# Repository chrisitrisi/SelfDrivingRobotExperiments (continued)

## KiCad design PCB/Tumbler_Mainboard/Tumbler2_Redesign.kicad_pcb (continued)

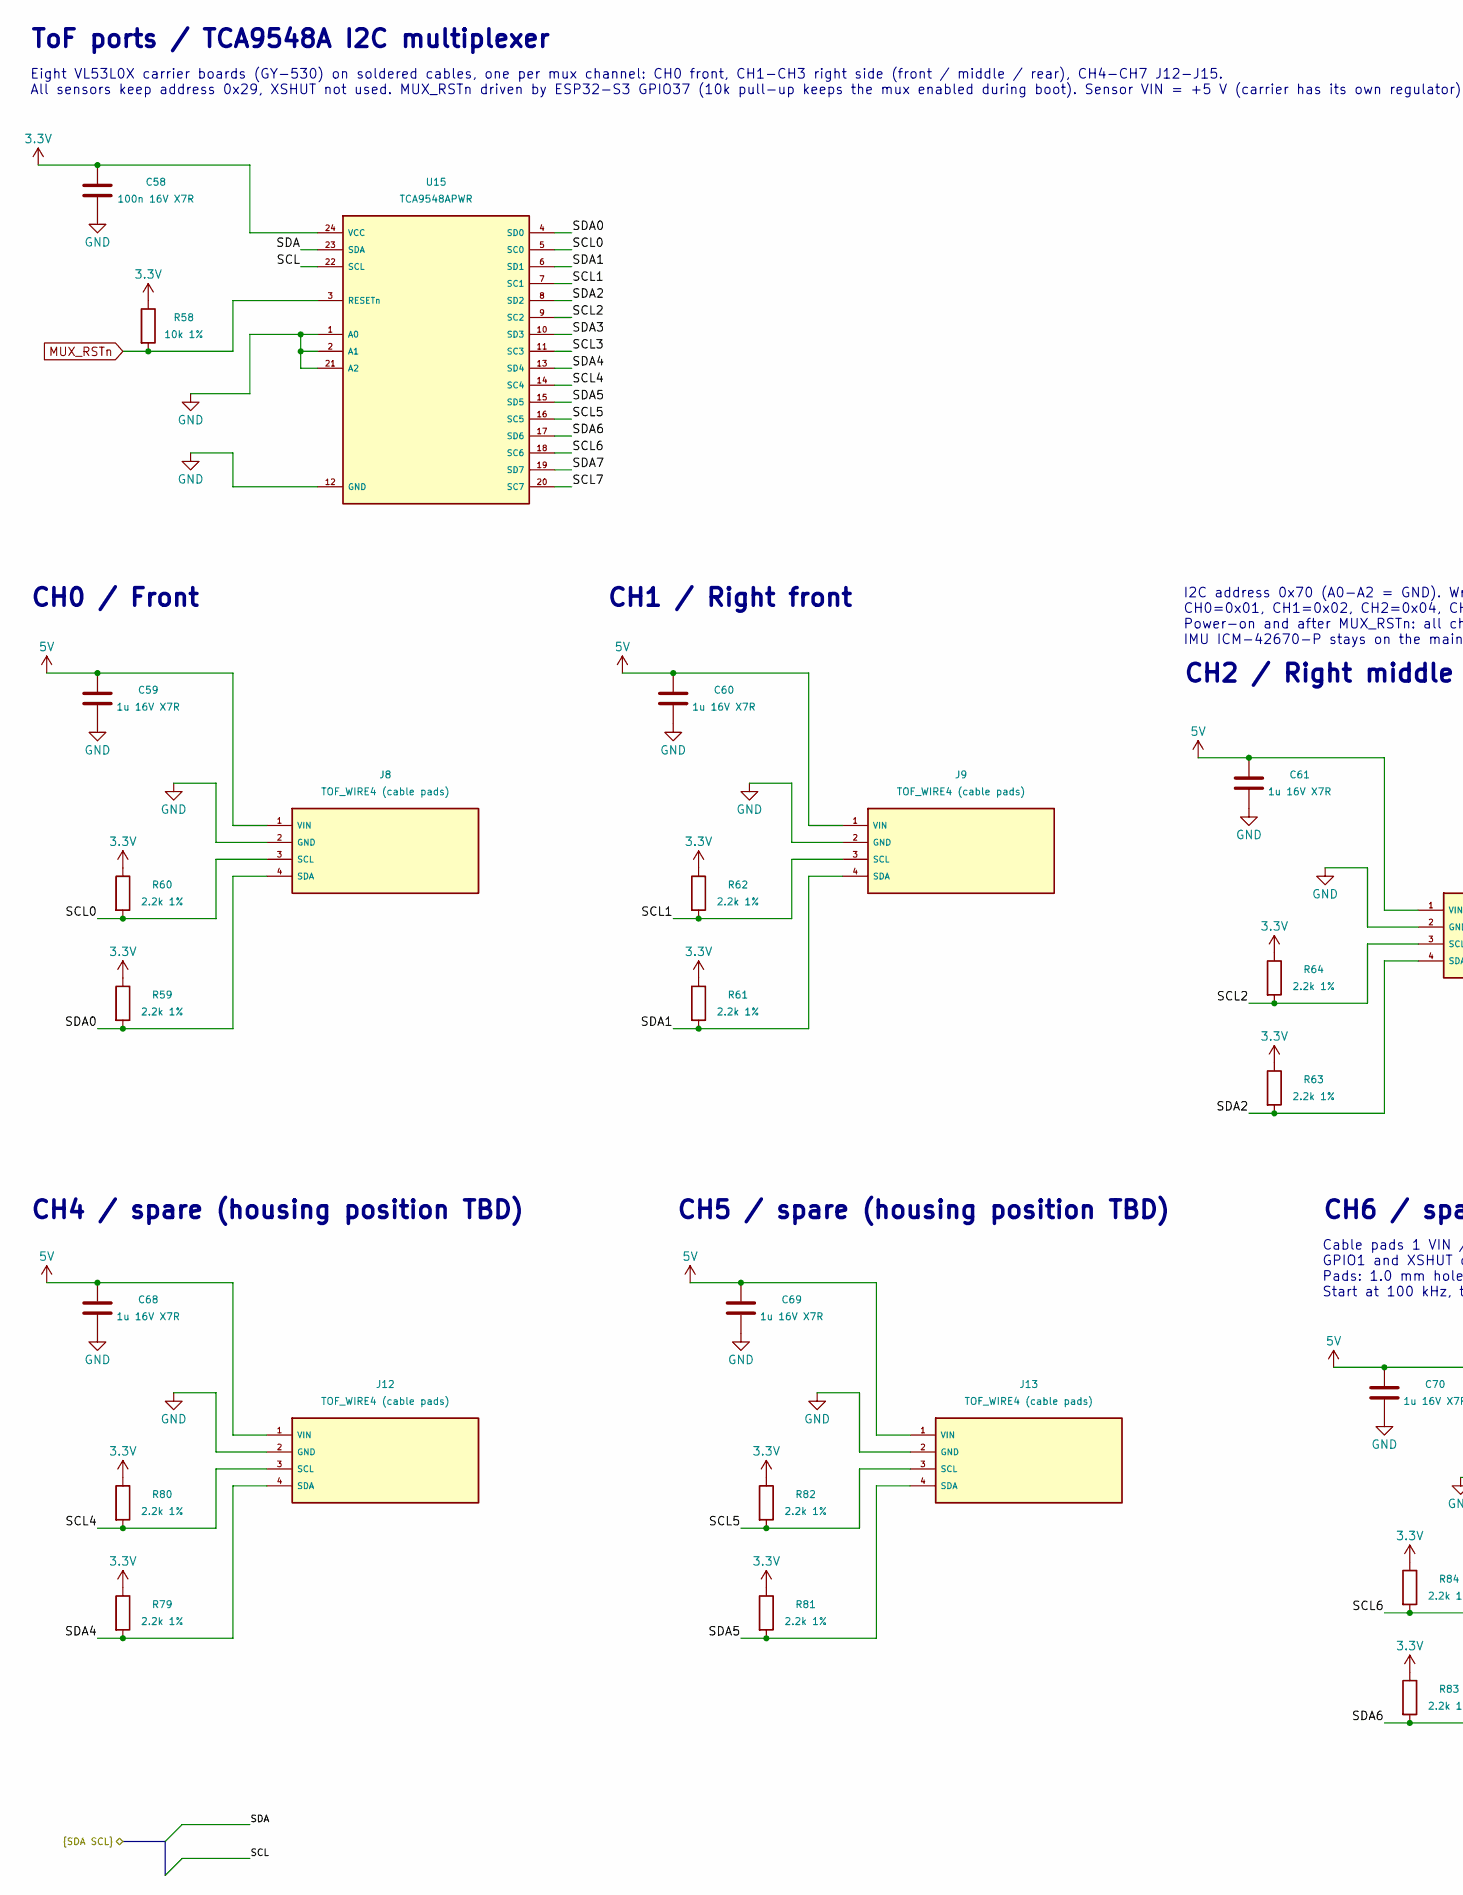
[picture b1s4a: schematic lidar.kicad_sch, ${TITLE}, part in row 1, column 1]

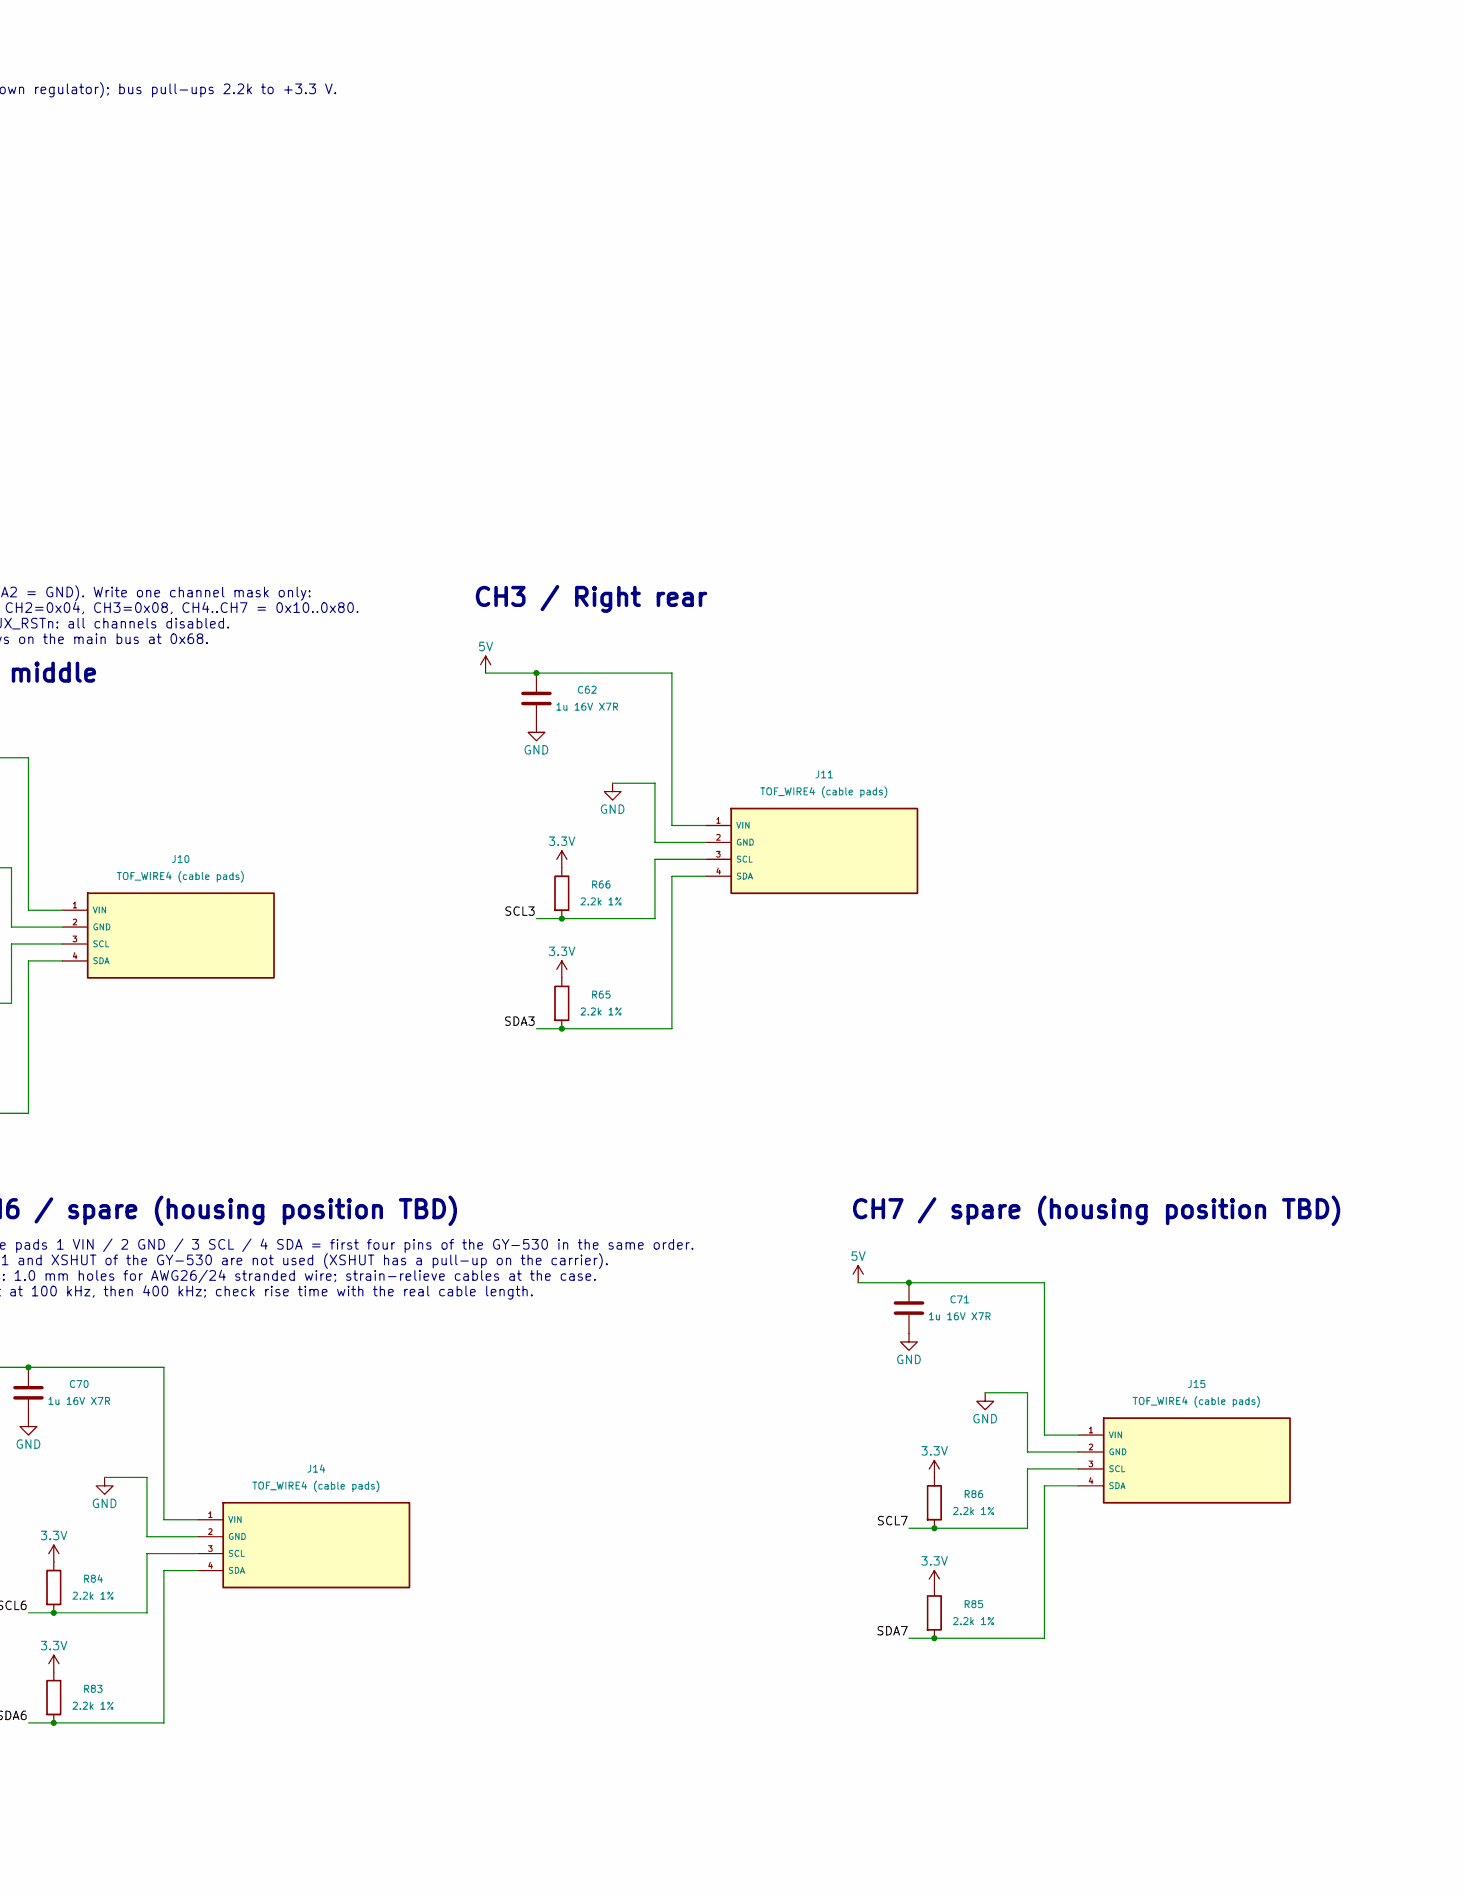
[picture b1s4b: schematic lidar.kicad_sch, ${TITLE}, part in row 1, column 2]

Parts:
C58: 100n 16V X7R; C_0603_1608Metric; LCSC PN C14663
C59, C60, C61, C62, C68, C69, C70, C71: 1u 16V X7R; C_0603_1608Metric; LCSC PN C59782
J8, J9, J10, J11, J12, J13, J14, J15: TOF_WIRE4 (cable pads); TOF_Wire_1x04_P2.54mm
R58: 10k 1%; R_0603_1608Metric; LCSC PN C25804
R59, R60, R61, R62, R63, R64, R65, R66, R79, R80, R81, R82, R83, R84, R85, R86: 2.2k 1%; R_0603_1608Metric; LCSC PN C4190
U15: TCA9548APWR; TSSOP-24_4.4x7.8mm_P0.65mm; LCSC PN C130026

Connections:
3.3V: C58.1, R58.1, R59.1, R60.1, R61.1, R62.1, R63.1, R64.1, R65.1, R66.1, R79.1, R80.1, R81.1, R82.1, R83.1, R84.1, R85.1, R86.1, U15.24 (VCC); also elsewhere on the board
5V: C59.1, C60.1, C61.1, C62.1, C68.1, C69.1, C70.1, C71.1, J8.1 (VIN), J9.1 (VIN), J10.1 (VIN), J11.1 (VIN), J12.1 (VIN), J13.1 (VIN), J14.1 (VIN), J15.1 (VIN); also elsewhere on the board
/LiDAR x8/SCL: U15.22 (SCL); also elsewhere on the board
/LiDAR x8/SCL0: J8.3 (SCL), R60.2, U15.5 (SC0)
/LiDAR x8/SCL1: J9.3 (SCL), R62.2, U15.7 (SC1)
/LiDAR x8/SCL2: J10.3 (SCL), R64.2, U15.9 (SC2)
/LiDAR x8/SCL3: J11.3 (SCL), R66.2, U15.11 (SC3)
/LiDAR x8/SCL4: J12.3 (SCL), R80.2, U15.14 (SC4)
/LiDAR x8/SCL5: J13.3 (SCL), R82.2, U15.16 (SC5)
/LiDAR x8/SCL6: J14.3 (SCL), R84.2, U15.18 (SC6)
/LiDAR x8/SCL7: J15.3 (SCL), R86.2, U15.20 (SC7)
/LiDAR x8/SDA: U15.23 (SDA); also elsewhere on the board
/LiDAR x8/SDA0: J8.4 (SDA), R59.2, U15.4 (SD0)
/LiDAR x8/SDA1: J9.4 (SDA), R61.2, U15.6 (SD1)
/LiDAR x8/SDA2: J10.4 (SDA), R63.2, U15.8 (SD2)
/LiDAR x8/SDA3: J11.4 (SDA), R65.2, U15.10 (SD3)
/LiDAR x8/SDA4: J12.4 (SDA), R79.2, U15.13 (SD4)
/LiDAR x8/SDA5: J13.4 (SDA), R81.2, U15.15 (SD5)
/LiDAR x8/SDA6: J14.4 (SDA), R83.2, U15.17 (SD6)
/LiDAR x8/SDA7: J15.4 (SDA), R85.2, U15.19 (SD7)
GND: C58.2, C59.2, C60.2, C61.2, C62.2, C68.2, C69.2, C70.2, C71.2, J8.2 (GND), J9.2 (GND), J10.2 (GND), J11.2 (GND), J12.2 (GND), J13.2 (GND), J14.2 (GND), J15.2 (GND), U15.1 (A0), U15.2 (A1), U15.12 (GND), U15.21 (A2); also elsewhere on the board
MUX_RSTn: R58.2, U15.3 (RESETn); also elsewhere on the board

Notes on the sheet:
Cable pads 1 VIN / 2 GND / 3 SCL / 4 SDA = first four pins of the GY-530 in the same order. GPIO1 and XSHUT of the GY-530 are not used (XSHUT has a pull-up on the carrier). Pads: 1.0 mm holes for AWG26/24 stranded wire; strain-relieve cables at the case. Start at 100 kHz, then 400 kHz; check rise t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
Eight VL53L0X carrier boards (GY-530) on soldered cables, one per mux channel: CH0 front, CH1-CH3 right side (front / middle / rear), CH4-CH7 J12-J15. All sensors keep address 0x29, XSHUT not used. MUX_RSTn driven by ESP32-S3 GPIO37 (10k pull-up keeps the mux enabled during boot). Sensor VIN = +5 V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
I2C address 0x70 (A0-A2 = GND). Write one channel mask only: CH0=0x01, CH1=0x02, CH2=0x04, CH3=0x08, CH4..CH7 = 0x10..0x80. Power-on and after MUX_RSTn: all channels disabled. IMU ICM-42670-P stays on the main bus at 0x68.
CH0 / Front
CH4 / spare (housing position TBD)
CH1 / Right front
ToF ports / TCA9548A I2C multiplexer
CH5 / spare (housing position TBD)
CH6 / spare (housing position TBD)
CH2 / Right middle
CH3 / Right rear
CH7 / spare (housing position TBD)

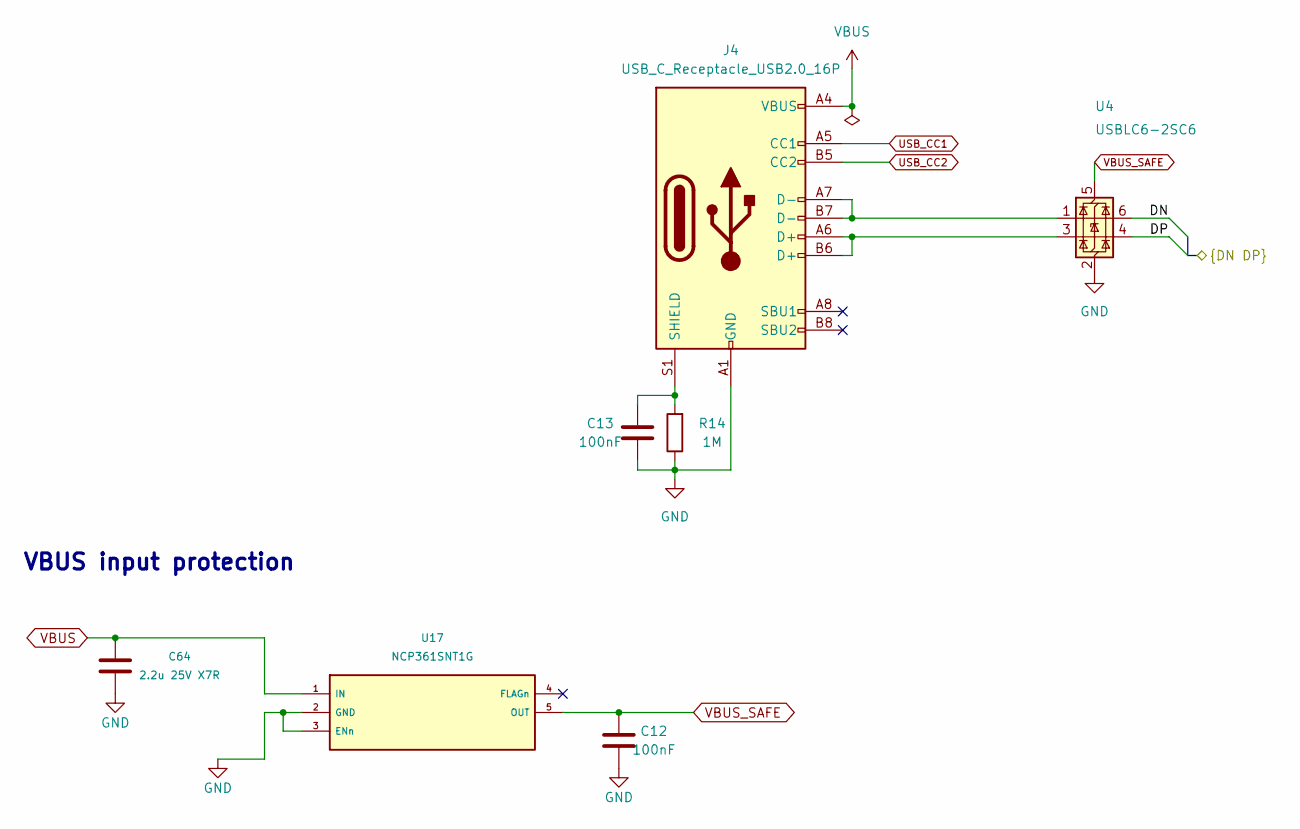
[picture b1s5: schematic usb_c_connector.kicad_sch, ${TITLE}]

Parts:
C12, C13: 100nF; C_0603_1608Metric; LCSC PN C14663
C64: 2.2u 25V X7R; C_0805_2012Metric; LCSC PN C19110
J4: USB_C_Receptacle_USB2.0_16P; KINGHELM_KH-TYPE-C-16P; LCSC PN C709357
R14: 1M; R_0603_1608Metric; LCSC PN C22935
U4: USBLC6-2SC6; SOT-23-6; LCSC PN C7519
U17: NCP361SNT1G; SOT-23-5; LCSC PN C233714

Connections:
/MCU/DN: U4.6 (I/O1); also elsewhere on the board
/MCU/DP: U4.4 (I/O2); also elsewhere on the board
GND: C12.2, C13.2, C64.2, J4.A1 (GND), J4.A12 (GND), J4.B1 (GND), J4.B12 (GND), R14.1, U4.2 (GND), U17.2 (GND), U17.3 (ENn); also elsewhere on the board
unnamed: J4.A6 (D+), J4.B6 (D+), U4.3 (I/O2)
unnamed: J4.A7 (D-), J4.B7 (D-), U4.1 (I/O1)
unnamed: C13.1, J4.S1 (SHIELD), R14.2
USB_CC1: J4.A5 (CC1); also elsewhere on the board
USB_CC2: J4.B5 (CC2); also elsewhere on the board
VBUS: C64.1, J4.A4 (VBUS), J4.A9 (VBUS), J4.B4 (VBUS), J4.B9 (VBUS), U17.1 (IN)
VBUS_SAFE: C12.1, U4.5 (VBUS), U17.5 (OUT); also elsewhere on the board

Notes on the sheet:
VBUS input protection

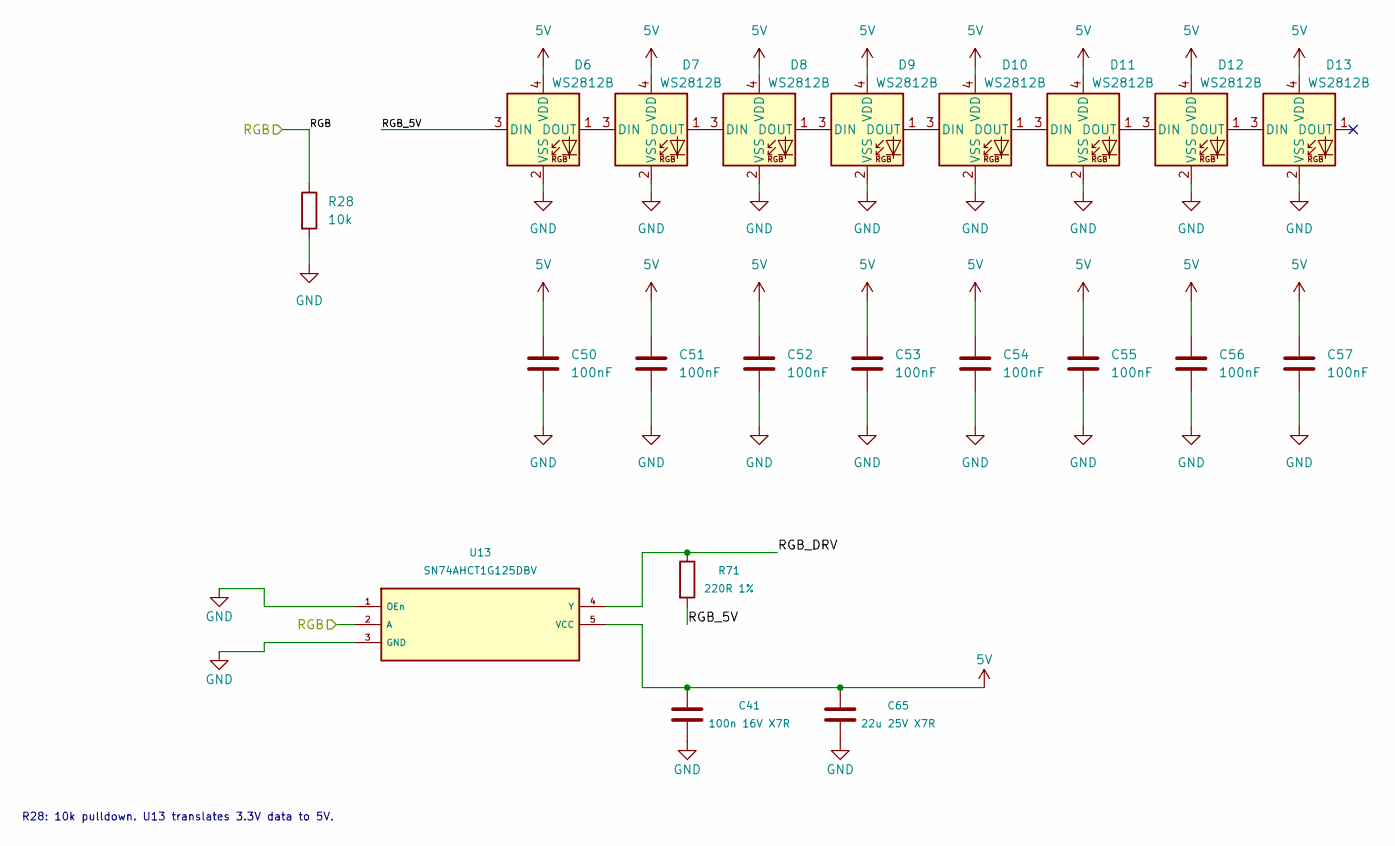
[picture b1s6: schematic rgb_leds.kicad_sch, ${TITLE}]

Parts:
C41: 100n 16V X7R; C_0603_1608Metric; LCSC PN C14663
C50, C51, C52, C53, C54, C55, C56, C57: 100nF; C_0603_1608Metric; LCSC PN C14663
C65: 22u 25V X7R; C_1210_3225Metric; LCSC PN C309062
D6, D7, D8, D9, D10, D11, D12, D13: WS2812B; LED_WS2812B-2020_PLCC4_2.0x2.0mm; LCSC PN C52917434
R28: 10k; R_0603_1608Metric; LCSC PN C25804
R71: 220R 1%; R_0603_1608Metric; LCSC PN C22962
U13: SN74AHCT1G125DBV; SOT-23-5; LCSC PN C7484

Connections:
5V: C41.1, C50.1, C51.1, C52.1, C53.1, C54.1, C55.1, C56.1, C57.1, C65.1, D6.4 (VDD), D7.4 (VDD), D8.4 (VDD), D9.4 (VDD), D10.4 (VDD), D11.4 (VDD), D12.4 (VDD), D13.4 (VDD), U13.5 (VCC); also elsewhere on the board
/RGB LEDs/RGB: R28.1, U13.2 (A); also elsewhere on the board
/RGB LEDs/RGB_5V: D6.3 (DIN), R71.2
/RGB LEDs/RGB_DRV: R71.1, U13.4 (Y)
GND: C41.2, C50.2, C51.2, C52.2, C53.2, C54.2, C55.2, C56.2, C57.2, C65.2, D6.2 (VSS), D7.2 (VSS), D8.2 (VSS), D9.2 (VSS), D10.2 (VSS), D11.2 (VSS), D12.2 (VSS), D13.2 (VSS), R28.2, U13.1 (OEn), U13.3 (GND); also elsewhere on the board
unnamed: D6.1 (DOUT), D7.3 (DIN)
unnamed: D7.1 (DOUT), D8.3 (DIN)
unnamed: D8.1 (DOUT), D9.3 (DIN)
unnamed: D9.1 (DOUT), D10.3 (DIN)
unnamed: D10.1 (DOUT), D11.3 (DIN)
unnamed: D11.1 (DOUT), D12.3 (DIN)
unnamed: D12.1 (DOUT), D13.3 (DIN)

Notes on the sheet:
R28: 10k pulldown. U13 translates 3.3V data to 5V.

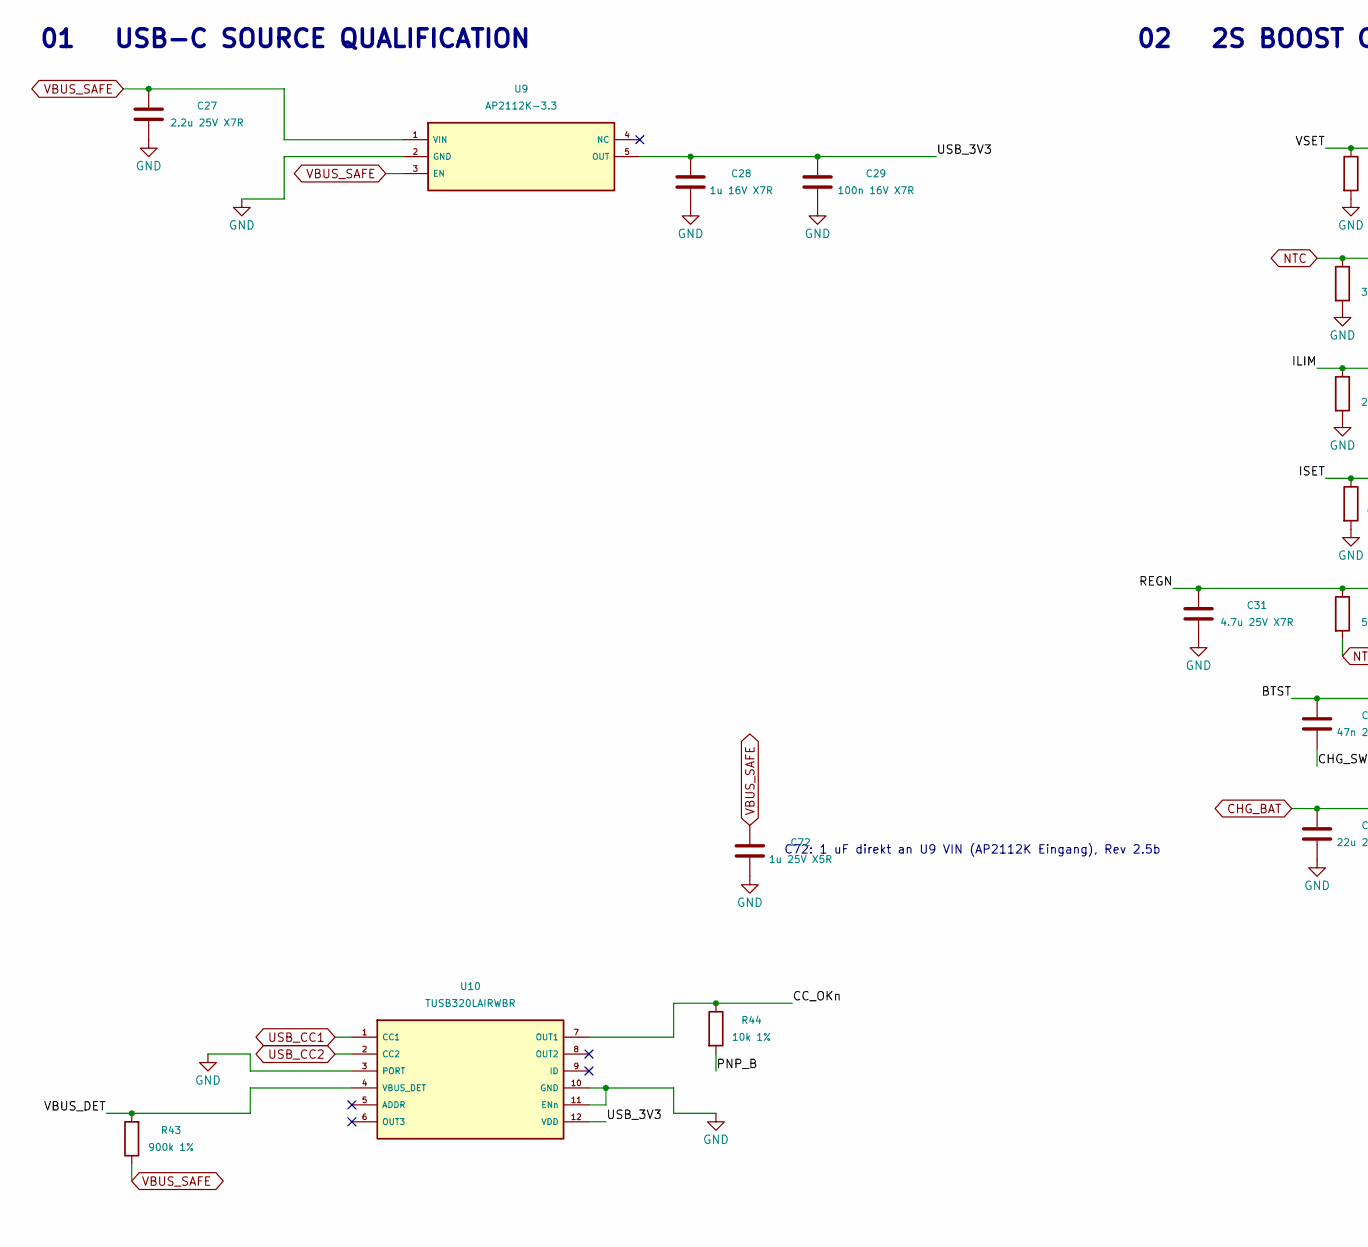
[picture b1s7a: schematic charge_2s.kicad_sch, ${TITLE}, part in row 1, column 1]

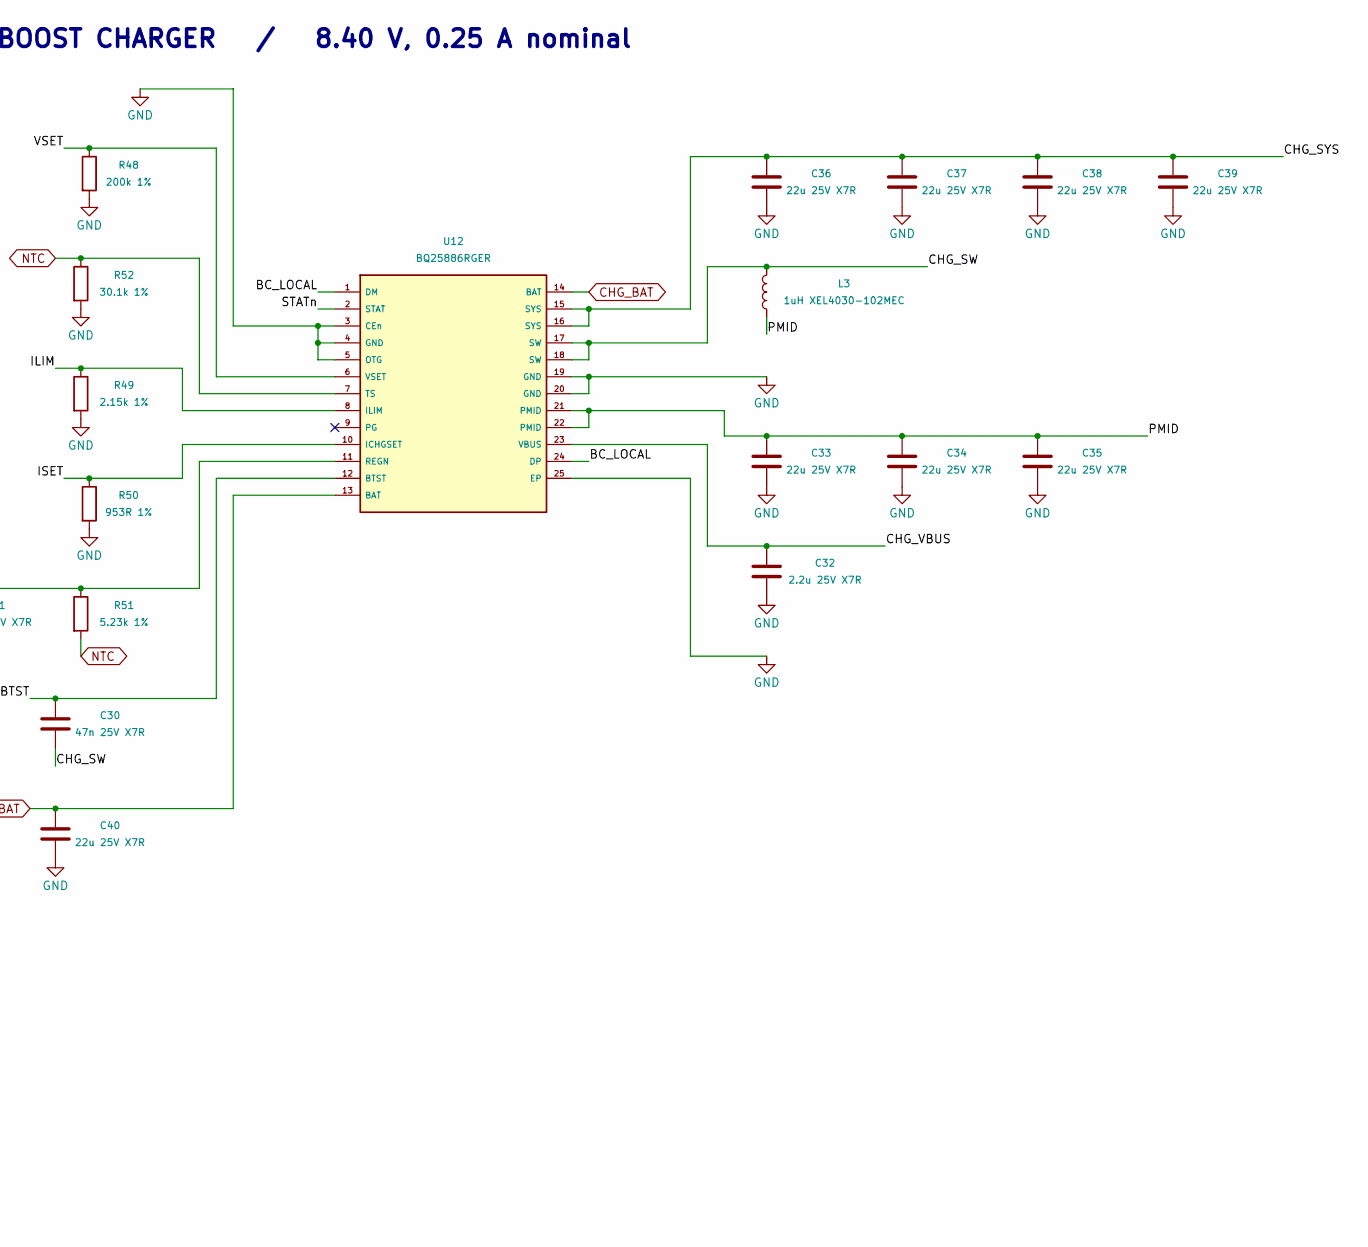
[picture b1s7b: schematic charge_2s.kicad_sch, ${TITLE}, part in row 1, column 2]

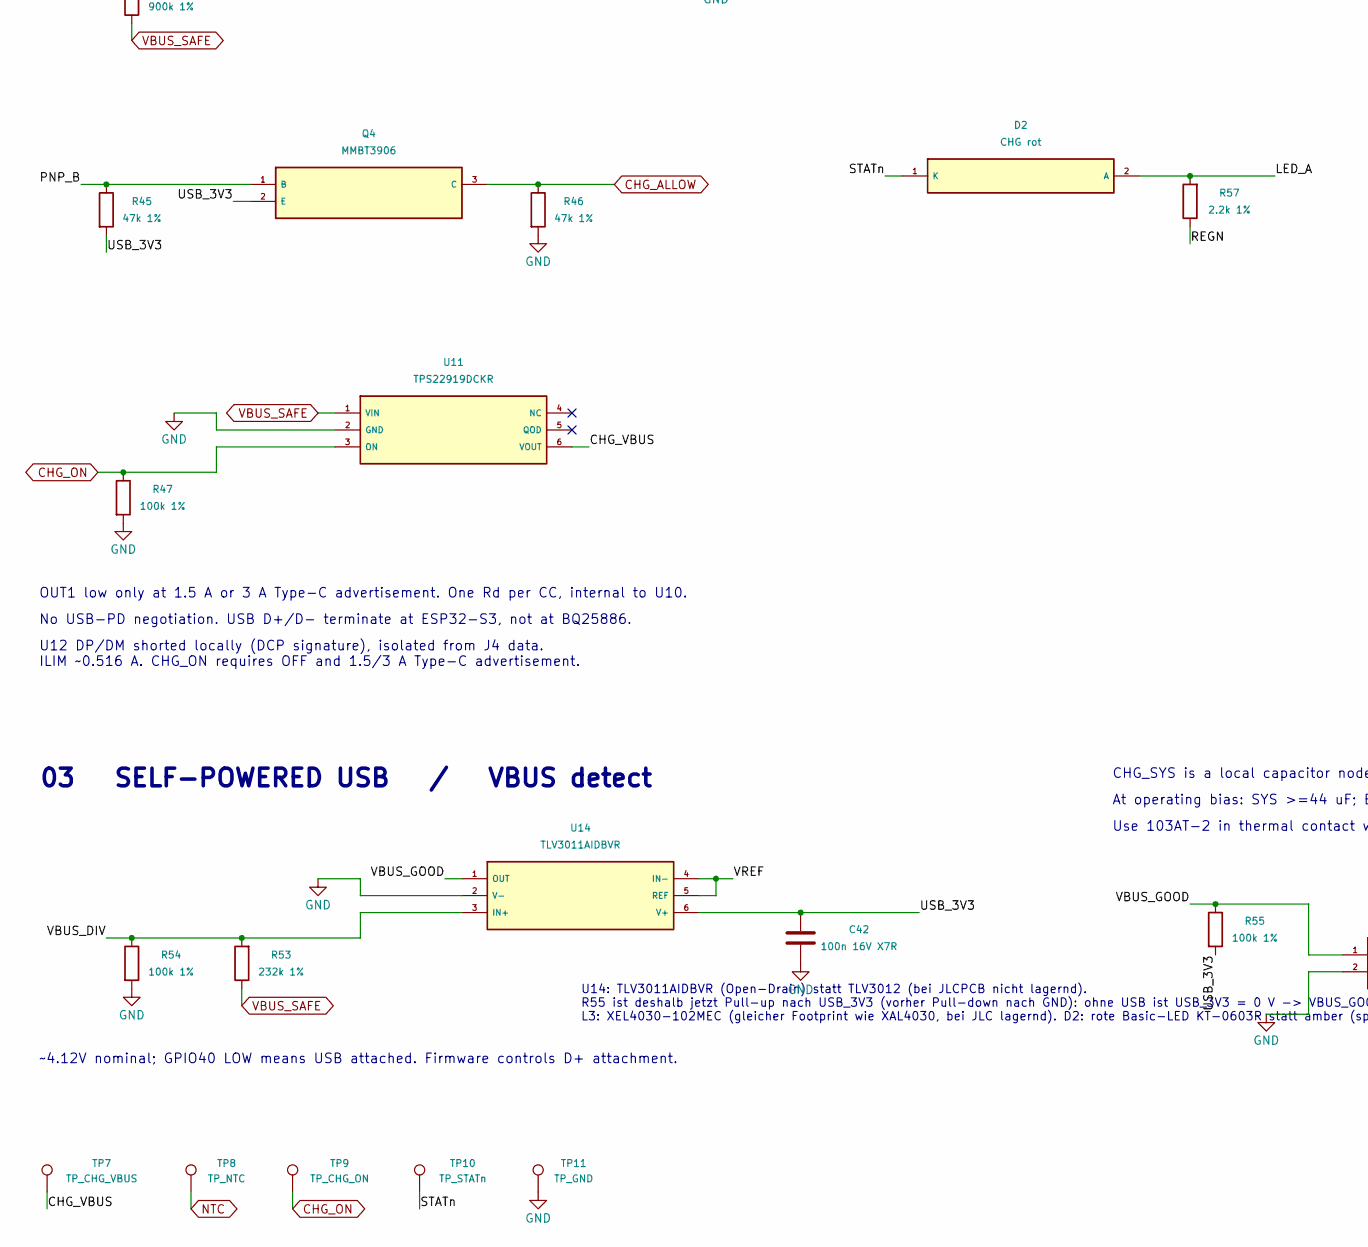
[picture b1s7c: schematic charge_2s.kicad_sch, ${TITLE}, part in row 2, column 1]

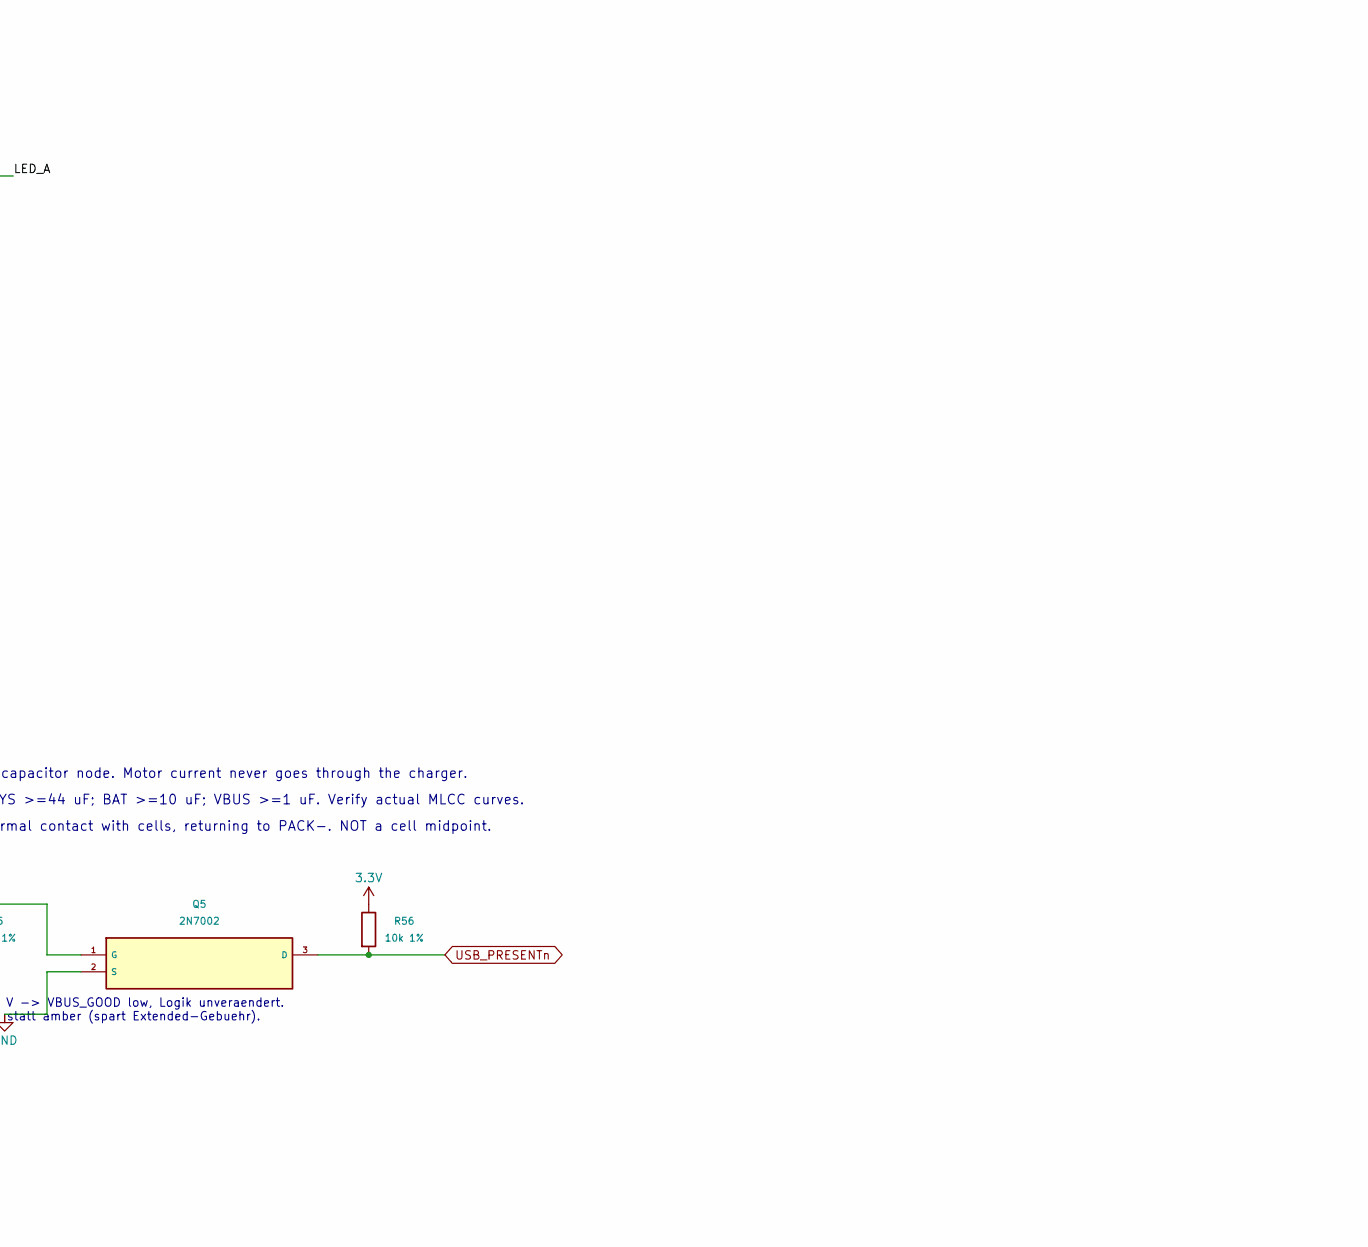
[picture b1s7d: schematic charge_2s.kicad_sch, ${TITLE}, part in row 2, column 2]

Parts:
C27, C32: 2.2u 25V X7R; C_0805_2012Metric; LCSC PN C19110
C28: 1u 16V X7R; C_0603_1608Metric; LCSC PN C59782
C29, C42: 100n 16V X7R; C_0603_1608Metric; LCSC PN C14663
C30: 47n 25V X7R; C_0603_1608Metric; LCSC PN C1622
C31: 4.7u 25V X7R; C_0805_2012Metric; LCSC PN C98195
C33, C34, C35, C36, C37, C38, C39, C40: 22u 25V X7R; C_1210_3225Metric; LCSC PN C309062
C72: 1u 25V X5R; C_0402_1005Metric; LCSC PN C52923
D2: CHG rot; LED_0603_1608Metric; LCSC PN C2286
L3: 1uH XEL4030-102MEC; L_Coilcraft_XAL4030-XXX; LCSC PN C5441341
Q4: MMBT3906; SOT-23; LCSC PN C2143
Q5: 2N7002; SOT-23; LCSC PN C8545
R43: 900k 1%; R_0603_1608Metric; LCSC PN C55585693
R44, R56: 10k 1%; R_0603_1608Metric; LCSC PN C25804
R45, R46: 47k 1%; R_0603_1608Metric; LCSC PN C25819
R47, R54, R55: 100k 1%; R_0603_1608Metric; LCSC PN C25803
R48: 200k 1%; R_0603_1608Metric; LCSC PN C25811
R49: 2.15k 1%; R_0402_1005Metric; LCSC PN C170259
R50: 953R 1%; R_0402_1005Metric; LCSC PN C172145
R51: 5.23k 1%; R_0603_1608Metric; LCSC PN C168333
R52: 30.1k 1%; R_0603_1608Metric; LCSC PN C23000
R53: 232k 1%; R_0603_1608Metric; LCSC PN C321799
R57: 2.2k 1%; R_0603_1608Metric; LCSC PN C4190
TP7: TP_CHG_VBUS; TestPoint_Pad_D1.0mm
TP8: TP_NTC; TestPoint_Pad_D1.0mm
TP9: TP_CHG_ON; TestPoint_Pad_D1.0mm
TP10: TP_STATn; TestPoint_Pad_D1.0mm
TP11: TP_GND; TestPoint_Pad_D1.0mm
U9: AP2112K-3.3; SOT-23-5; LCSC PN C51118
U10: TUSB320LAIRWBR; TI_RWB0012A; LCSC PN C132554
U11: TPS22919DCKR; SOT-363_SC-70-6; LCSC PN C2149796
U12: BQ25886RGER; Texas_RGE0024H_VQFN-24-1EP_4x4mm_P0.5mm_EP2.7x2.7mm; LCSC PN C2765094
U14: TLV3011AIDBVR; SOT-23-6; LCSC PN C2870632

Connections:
3.3V: R56.1; also elsewhere on the board
/USB-C / 2S charger/BC_LOCAL: U12.1 (DM), U12.24 (DP)
/USB-C / 2S charger/BTST: C30.1, U12.12 (BTST)
/USB-C / 2S charger/CC_OKn: R44.1, U10.7 (OUT1)
/USB-C / 2S charger/CHG_SW: C30.2, L3.2, U12.17 (SW), U12.18 (SW)
/USB-C / 2S charger/CHG_SYS: C36.1, C37.1, C38.1, C39.1, U12.15 (SYS), U12.16 (SYS)
/USB-C / 2S charger/CHG_VBUS: C32.1, TP7.1, U11.6 (VOUT), U12.23 (VBUS)
/USB-C / 2S charger/ILIM: R49.1, U12.8 (ILIM)
/USB-C / 2S charger/ISET: R50.1, U12.10 (ICHGSET)
/USB-C / 2S charger/LED_A: D2.2 (A), R57.2
/USB-C / 2S charger/PMID: C33.1, C34.1, C35.1, L3.1, U12.21 (PMID), U12.22 (PMID)
/USB-C / 2S charger/PNP_B: Q4.1 (B), R44.2, R45.1
/USB-C / 2S charger/REGN: C31.1, R51.1, R57.1, U12.11 (REGN)
/USB-C / 2S charger/STATn: D2.1 (K), TP10.1, U12.2 (STAT)
/USB-C / 2S charger/USB_3V3: C28.1, C29.1, C42.1, Q4.2 (E), R45.2, R55.2, U9.5 (OUT), U10.12 (VDD), U14.6 (V+)
/USB-C / 2S charger/VBUS_DET: R43.2, U10.4 (VBUS_DET)
/USB-C / 2S charger/VBUS_DIV: R53.2, R54.1, U14.3 (IN+)
/USB-C / 2S charger/VBUS_GOOD: Q5.1 (G), R55.1, U14.1 (OUT)
/USB-C / 2S charger/VREF: U14.4 (IN-), U14.5 (REF)
/USB-C / 2S charger/VSET: R48.1, U12.6 (VSET)
CHG_ALLOW: Q4.3 (C), R46.1; also elsewhere on the board
CHG_BAT: C40.1, U12.13 (BAT), U12.14 (BAT); also elsewhere on the board
CHG_ON: R47.1, TP9.1, U11.3 (ON); also elsewhere on the board
GND: C27.2, C28.2, C29.2, C31.2, C32.2, C33.2, C34.2, C35.2, C36.2, C37.2, C38.2, C39.2, C40.2, C42.2, C72.2, Q5.2 (S), R46.2, R47.2, R48.2, R49.2, R50.2, R52.2, R54.2, TP11.1, U9.2 (GND), U10.3 (PORT), U10.10 (GND), U10.11 (ENn), U11.2 (GND), U12.3 (CEn), U12.4 (GND), U12.5 (OTG), U12.19 (GND), U12.20 (GND), U12.25 (EP), U14.2 (V-); also elsewhere on the board
NTC: R51.2, R52.1, TP8.1, U12.7 (TS)
USB_CC1: U10.1 (CC1); also elsewhere on the board
USB_CC2: U10.2 (CC2); also elsewhere on the board
USB_PRESENTn: Q5.3 (D), R56.2; also elsewhere on the board
VBUS_SAFE: C27.1, C72.1, R43.1, R53.1, U9.1 (VIN), U9.3 (EN), U11.1 (VIN); also elsewhere on the board

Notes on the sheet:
CHG_SYS is a local capacitor node. Motor current never goes through the charger.
At operating bias: SYS >=44 uF; BAT >=10 uF; VBUS >=1 uF. Verify actual MLCC curves.
No USB-PD negotiation. USB D+/D- terminate at ESP32-S3, not at BQ25886.
01 USB-C SOURCE QUALIFICATION
Use 103AT-2 in thermal contact with cells, returning to PACK-. NOT a cell midpoint.
~4.12V nominal; GPIO40 LOW means USB attached. Firmware controls D+ attachment.
U12 DP/DM shorted locally (DCP signature), isolated from J4 data. ILIM ~0.516 A. CHG_ON requires OFF and 1.5/3 A Type-C advertisement.
03 SELF-POWERED USB / VBUS detect
02 2S BOOST CHARGER / 8.40 V, 0.25 A nominal
OUT1 low only at 1.5 A or 3 A Type-C advertisement. One Rd per CC, internal to U10.
C72: 1 uF direkt an U9 VIN (AP2112K Eingang), Rev 2.5b
U14: TLV3011AIDBVR (Open-Drain) statt TLV3012 (bei JLCPCB nicht lagernd). R55 ist deshalb jetzt Pull-up nach USB_3V3 (vorher Pull-down nach GND): ohne USB ist USB_3V3 = 0 V -> VBUS_GOOD low, Logik unveraendert. L3: XEL4030-102MEC (gleicher Footprint wie XAL4030, bei JLC lagernd). D2: rote Basic-LED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
